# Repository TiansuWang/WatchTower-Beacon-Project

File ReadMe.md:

This project is the work done by Tiansu Wang During the internship in WatchTower Robotics(https://www.wtrco.com).

#

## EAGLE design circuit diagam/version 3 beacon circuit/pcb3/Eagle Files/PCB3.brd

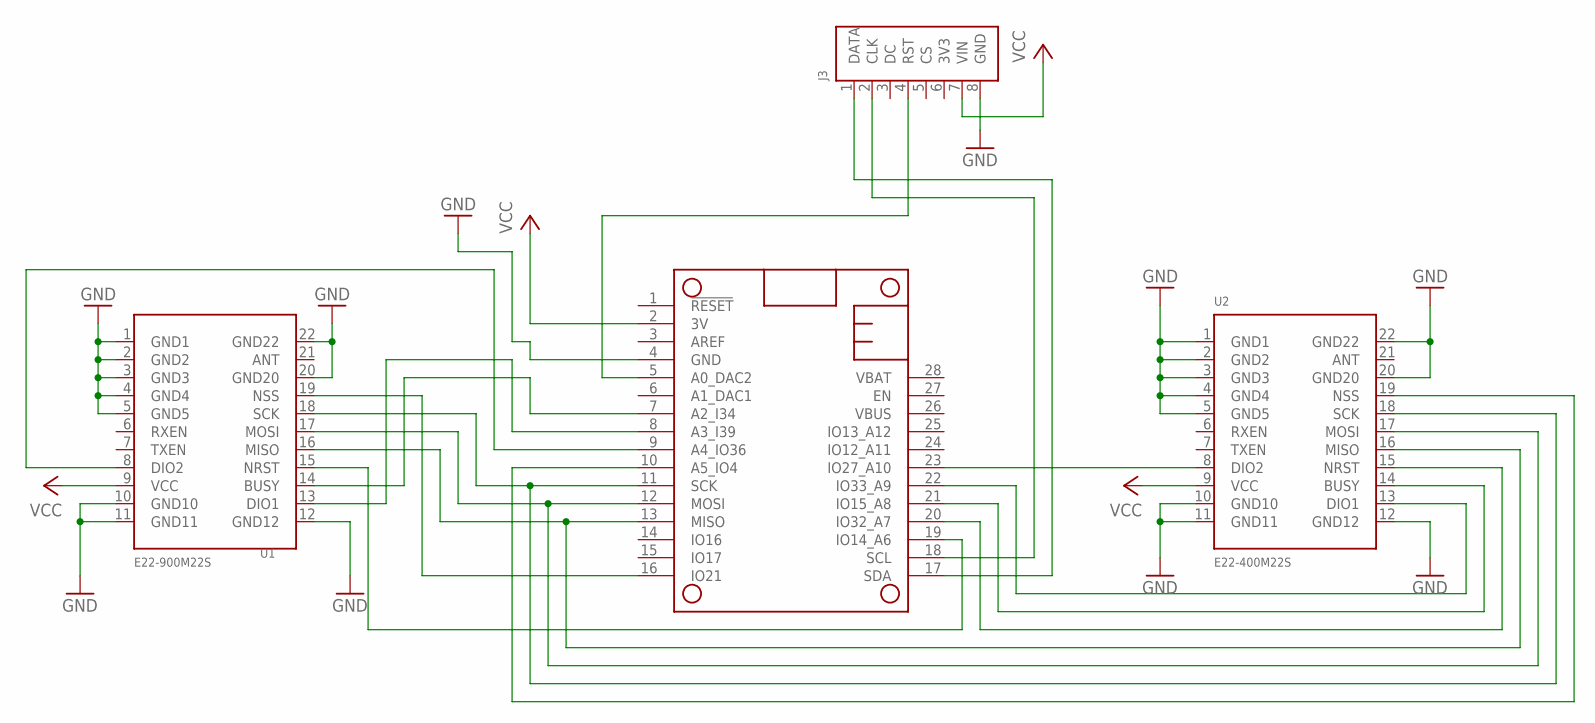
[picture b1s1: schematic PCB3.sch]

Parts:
J3: 1.3"_128X64; 1.3"_128X64_OLED
MS1: FEATHERWING
U1: E22-900M22S; E22
U2: E22-400M22S; E22

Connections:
3V3: J3.6 (3V3)
400BUSY: MS1.21 (IO15_A8), U2.14 (BUSY)
400CS: MS1.10 (A5_IO4), U2.19 (NSS)
400NRESET: MS1.20 (IO32_A7), U2.15 (NRST)
400RXINT: MS1.22 (IO33_A9), U2.13 (DIO1)
400TXINT: MS1.23 (IO27_A10), U2.8 (DIO2)
900BUSY: MS1.7 (A2_I34), U1.14 (BUSY)
900CS: MS1.16 (IO21), U1.19 (NSS)
900RXINT: MS1.8 (A3_I39), U1.13 (DIO1)
900TXINT: MS1.9 (A4_IO36), U1.8 (DIO2)
GND: J3.8 (GND), MS1.4 (GND), U1.1 (GND1), U1.2 (GND2), U1.3 (GND3), U1.4 (GND4), U1.5 (GND5), U1.10 (GND10), U1.11 (GND11), U1.12 (GND12), U1.20 (GND20), U1.22 (GND22), U2.1 (GND1), U2.2 (GND2), U2.3 (GND3), U2.4 (GND4), U2.5 (GND5), U2.10 (GND10), U2.11 (GND11), U2.12 (GND12), U2.20 (GND20), U2.22 (GND22)
MISO: MS1.13 (MISO), U1.16 (MISO), U2.16 (MISO)
MOSI: MS1.12 (MOSI), U1.17 (MOSI), U2.17 (MOSI)
unnamed: J3.2 (CLK), MS1.18 (SCL)
unnamed: J3.1 (DATA), MS1.17 (SDA)
unnamed: MS1.19 (IO14_A6), U1.15 (NRST)
RST: J3.4 (RST), MS1.5 (A0_DAC2)
SCK: MS1.11 (SCK), U1.18 (SCK), U2.18 (SCK)
VCC: J3.7 (VIN), MS1.2 (3V), U1.9 (VCC), U2.9 (VCC)

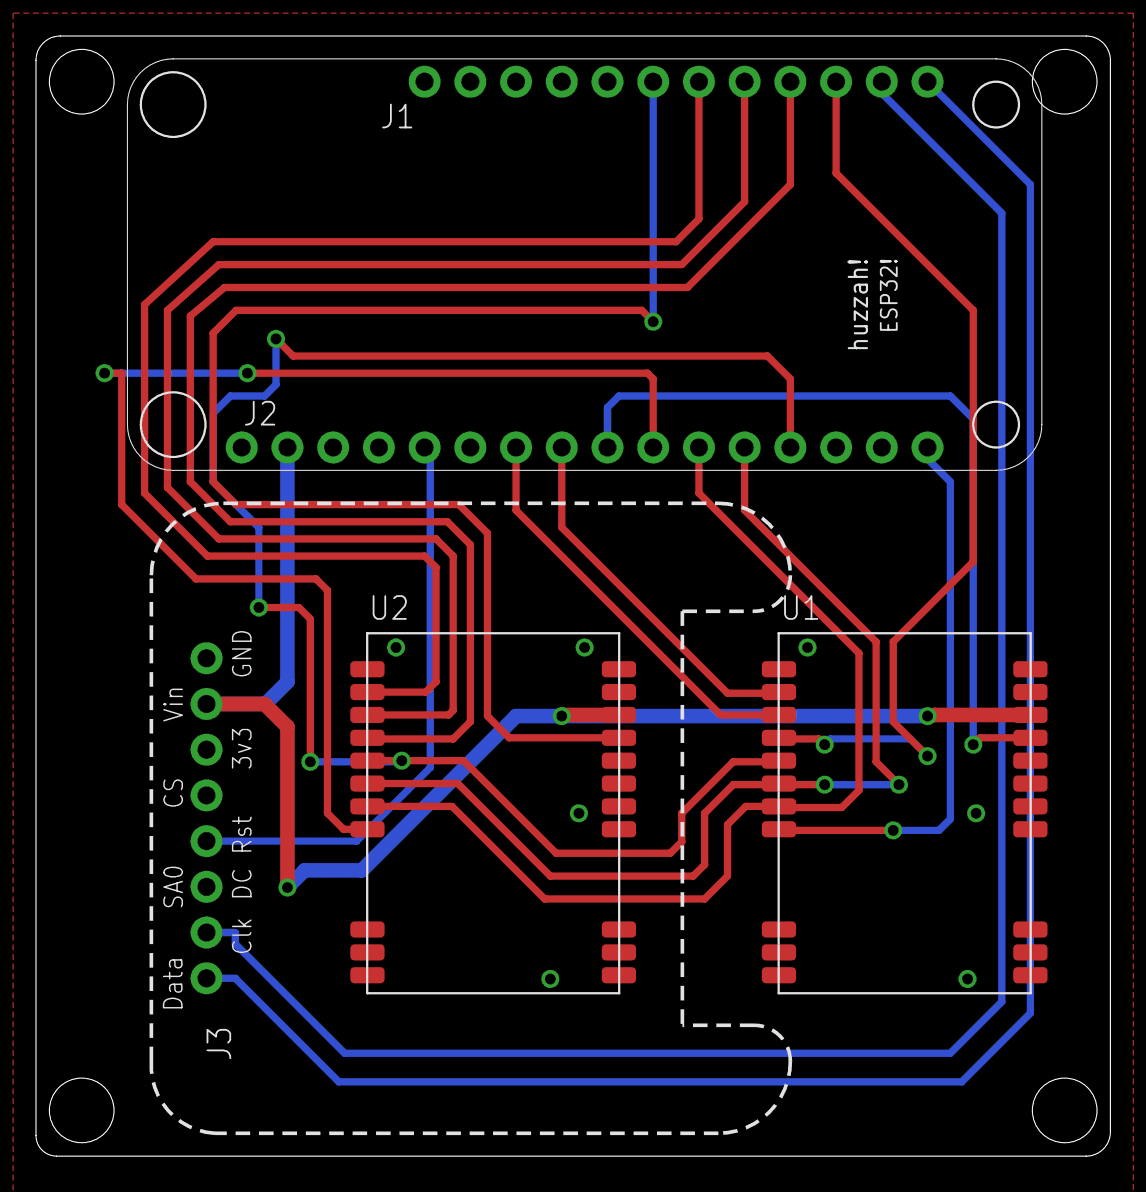
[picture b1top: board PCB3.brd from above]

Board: 2 copper layers, 59.7 x 62.2 mm, 4 parts (0 on the bottom side), 18 nets.

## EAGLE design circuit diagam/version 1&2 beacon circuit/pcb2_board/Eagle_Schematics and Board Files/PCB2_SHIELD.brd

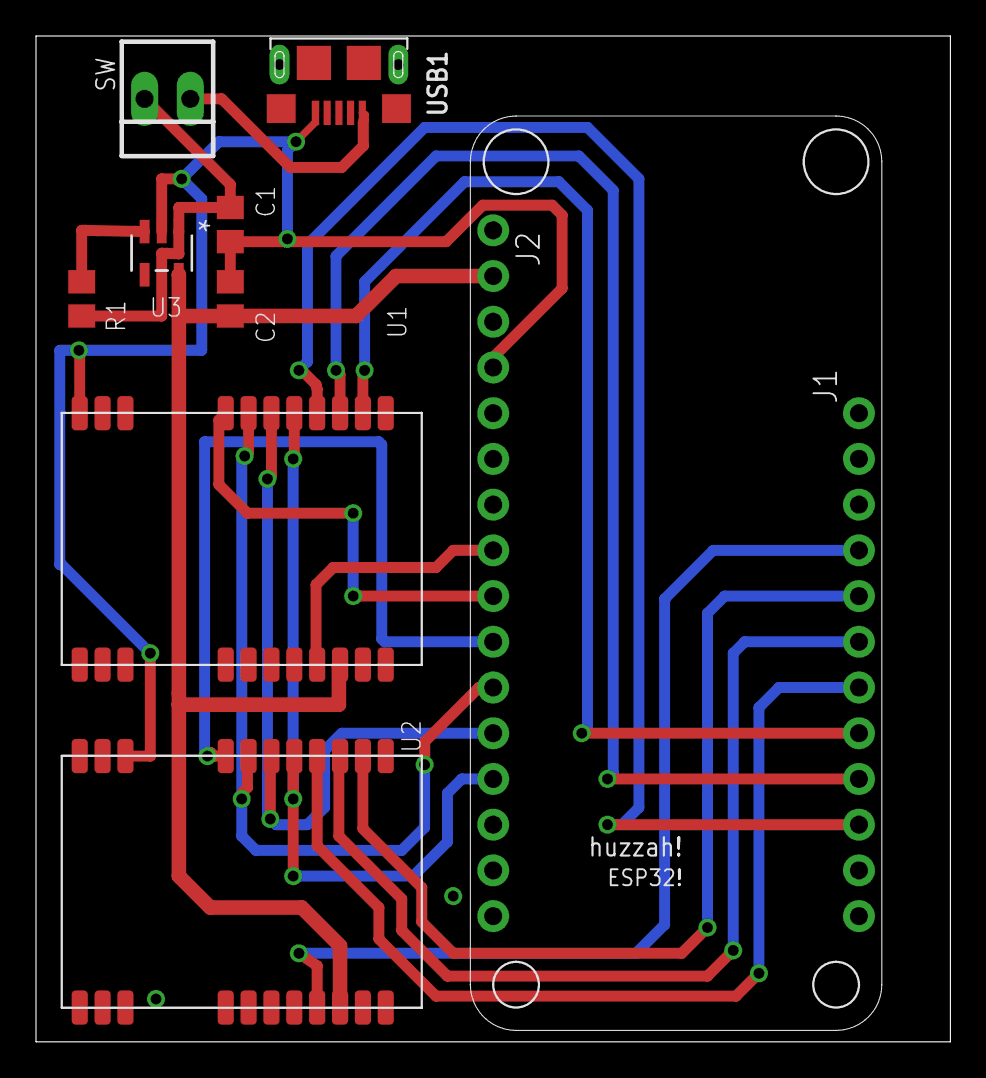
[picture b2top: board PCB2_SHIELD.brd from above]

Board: 2 copper layers, 50.8 x 55.9 mm, 9 parts (0 on the bottom side), 17 nets.

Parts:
C1, C2: C0805
MS1: FEATHERWING
R1: R0805
SW: 22-23-2021
U1: E22-900M22S; E22
U2: E22-400M22S; E22
U3: AP2112; SOT25
USB1: USB; 10118193-0001LF

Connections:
GND: C1.2, C2.2, MS1.4, U1.1, U1.2, U1.3, U1.4, U1.5, U1.10, U1.11, U1.12, U1.20, U1.22, U2.1, U2.2, U2.3, U2.4, U2.5, U2.10, U2.11, U2.12, U2.20, U2.22, U3.2, USB1.GND
unnamed: MS1.9, U1.19
unnamed: MS1.11, U1.18, U2.18
unnamed: MS1.12, U1.17, U2.17
unnamed: MS1.13, U1.16, U2.16
unnamed: MS1.19, U1.15
unnamed: MS1.20, U1.14
unnamed: MS1.21, U1.13
unnamed: MS1.8, U1.8
unnamed: MS1.25, U2.8
unnamed: MS1.24, U2.13
unnamed: MS1.23, U2.14
unnamed: MS1.22, U2.15
unnamed: MS1.10, U2.19
unnamed: C1.1, R1.1, SW.2, U3.1
unnamed: R1.2, SW.1, U3.3, USB1.VBUS
VCC: C2.1, MS1.2, U1.9, U2.9, U3.5

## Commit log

2019-07-08 Just created this project, upload all the things into the git.
